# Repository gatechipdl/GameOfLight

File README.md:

# GameOfLight
Game of Light Installation

## Requirements
- 36 stations
- each station 1m in lenght covered in leds
- 5 sections of lamp to create a 'species'
- automatic identification of each lamp 'species'

## Location
- Hyatt Regency Denver at Co Convention Center
    - [Floorplans](https://denver.regency.hyatt.com/hyatt/images/hotels/dencc/floorplan.pdf)

## Main Power Supply
- 12,24V power supply recommended with a buck converter (for leds and mcu) or linear regulator (if for just mcu) at each location
- typical computer psu will have several 12V rails. A [modular](https://www.amazon.com/EVGA-Supernova-120-G1-1000-VR-Modular-Supply/dp/B00CGYCNG2) psu would be best for ensuring enough 12V rails without extra wiring.
- if there is 5m of leds with 30 leds/meter wrapped around a tube, then that is 150 leds. 150 leds at 60mA is 9A running at around 3V. This is around 27-30W assuming an efficient local conversion of power, which is likely embedded within the addressable chip.
- 36 stations of 30W is a total max draw of 1080W. So a 800W-1000W-1200W power supply should be fine.

## Local Power Regulation
- Switch mode power supply for high current, such as this [300W Step Down Regulator](https://www.aliexpress.com/item/DC-CC-12A-300W-Step-Down-Buck-Converter-7-32V-To-0-8-28V-Power-module/32247251105.html)
- Linear regulator for low current needs (eg. if using 12V main power supply and 12V leds)

## Power Distribution Connectors
- ribbon cable (40 pin), using most pins for power and ground
- RJ45 can only handle up to 1A
- RJ11 can only handle up to 1A
- 5557 molex need to crimp; not designed to be removed often;
- DC Barrel Jack 5.5mm, most connectors designed for 3A, but can get special ones for laptaps that can handle 8A
- [6 pin Pluggable Screw Terminal](https://www.aliexpress.com/item/Free-shipping-5-sets-ht5-08-6pin-Terminal-plug-type-300V-10A-5-08mm-pitch-connector/32667091061.html)
    - 12V - GND - DataMinus - DataPlus - GND - 12V
- [7 pin Pluggable Screw Terminal](https://www.aliexpress.com/item/Free-shipping-5-sets-ht5-08-7pin-Terminal-plug-type-300V-10A-5-08mm-pitch-connector/32665369867.html)
    - 12V - GND - DataMinus - GND - DataPlus - GND - 12V
    - extra ground in middle is for connecting ground to the main controller in the case that the main controller is not using the same ground as the stations' ground from the main power supply. For example if the main controller is run by or powered by a laptop.

## Power Distribution Wiring
- [$27 100 ft. 14/2 White Solid SIMpull NM-B Wire](http://www.homedepot.com/p/Romex-100-ft-14-2-White-Solid-SIMpull-NM-B-Wire-28827428/202316379)
- [$38 100 ft. 14-2 Black Stranded Landscape Lighting Cable](http://www.homedepot.com/p/Southwire-100-ft-14-2-Black-Stranded-Landscape-Lighting-Cable-55213243/202316247)
- [$16 100' Feet 14 Gauge Red Black Stranded 2 Conductor Speaker Wire Car Home Audio Ga](https://www.amazon.com/Gauge-Black-Stranded-Conductor-Speaker/dp/B00J36SUWC)
- [$26 eXtreme Products 2 Conductor 14 Gauge Stranded Copper Core Speaker Wire (No Aluminum Core) for Home Theater Speakers Radio Speakers Car Audio or Any Audio Interface - 100 Foot Clear Coat](https://www.amazon.com/eXtreme-Conductor-Speaker-Wire-Interface/dp/B01HBWJ1HM)

## Signal Distribution Wiring
- for RS485 we need overall impedance of 120 ohms. For our distances, lighter gauges are fine, but [this](http://www.chipkin.com/rs485-cables-why-you-need-3-wires-for-2-two-wire-rs485/) recommends 24AWG or heavier. [Here are more recommendations](http://www.bb-elec.com/Learning-Center/All-White-Papers/Serial/Cable-Selection-for-RS422-and-RS485-Systems/Cable-Selection-for-RS-422-and-RS-485-Systems.PDF).
- Two wire or Three wire. May need three wire to include an additional ground in the case that the main controller is not using the same ground as the stations' power ground from the main power supply. This could be the case with a laptop for example.
- [$13 Ethernet Cable (100 Feet)](https://www.amazon.com/Mediabridge-Ethernet-Cable-100-Feet/dp/B003RCEAB8), cut and pull out twisted pair wires
- [$23 100-Feet 24-Gauge 4 Pair Cat 5e](https://www.amazon.com/Southwire-56917643-100-Feet-Outdoor-CMR-75-Degree/dp/B005V0BJ1S)

## LEDs
- addressable color leds
- could use 1 2m strip folded over
- could use 1 5m strip wrapped around a pole (this will provide more light)
- WS2811 with 3 color leds on each section, each led is rgb, but in clusters of 3. This is fine for our applications. Also these are 12V, which is better for current draw. [$8-10 per 5m strip](https://www.aliexpress.com/item/best-price-5m-DC12V-ws2811ic-5050-RGB-SMD-individually-addressable-ws2811-led-pixels-strip/32385533484.html)

## Control
- recommended individual controller for each station; otherwise refresh rate is likely to be very slow
- attiny85 possible? may not have enough pins; but might
- atmega328p?
- arduino pro mini clone ($1-2)
- 1 master device with 36 other devices. The master controls the CA simulation and dictates the animation colors and patterns to each of the 36 stations.
    - however, it is possible to have the 36 devices run the simulation themselves, with each device getting data about it's neighbors, and computing the next step and selecting it's own animation. This would also require that they all synchronize, to some degree on an update algorithm. This could be done. Would be really nice to have. This is something we could first develop in the master/slave configuration, and then later spend time developing the slave-only method if there is time. The slave-only would really connect conceptually rather than having any kind of single master.

## Recognition
- manual input (what a drag)
- infrared linear quadrature encoder or similar to recognize the lamp 'species' as a barcode when the lamp shade is slide over the rod
    - this would argue for a separate controller on each station
- IR Distance Sensor
    - [XK-GK-5010A](https://www.aliexpress.com/item/Hot-Sale-Short-Distance-Sensor-Induction-Switch-Dual-Functions-Ir-Sensor-Switch-Active-Performance-Modules-Board/32769983297.html)
    - [TCRT5000 Sensor](https://www.aliexpress.com/item/20-pcs-TCRT5000L-TCRT5000-Reflective-Optical-Sensor-Infrared-IR-Photoelectric-Switch/1909098476.html)
    - [TCRT5000 Module with Pot](https://www.aliexpress.com/item/Free-shipping-Line-Track-Sensor-TCRT5000-Infrared-Reflective-IR-Photoelectric-Switch-Barrier/32517344067.html) [3D model](http://www.stlfinder.com/model/line-finder-tcrt5000/4505787) 32mmx14mm
    - [TCRT5000 Module Digital Only](https://www.aliexpress.com/item/New-TCRT5000-Line-Track-Sensor-Module-Reflection-Infrared-Sensor-Switch-Module-For-Arduino-5pcs-lot-Free/32359412782.html)
    - [TCRT5000 Module Analog Only](https://www.aliexpress.com/item/10PCS-IR-Infrared-Line-Track-Follower-Sensor-TCRT5000-Obstacle-Avoidanc-For-Arduino/32672744833.html)
    - [4 Channel Line Follower](https://www.aliexpress.com/item/Free-shipping-4-way-infrared-tracing-line-follow-tracking-obatacle-avoidance-Sensor-Module-for-Aduino-Robot/32645816426.html)
    - [8 Channel Line Follower](https://www.aliexpress.com/item/8-Channel-High-Precision-Infrared-Detection-Tracking-Sensor-Moudle-For-Arduino-Raspberry-Pi-Car-Robot-TCRT5000/32714804808.html)

## Communication
- if using multiple controllers, one on each station, using a [multidrop bus](https://en.wikipedia.org/wiki/Multidrop_bus) rather than a shift/ring topology
- I2C can go about [20ft](http://forum.arduino.cc/index.php?topic=57604.0) without additional driver or buffers
- RS-232 can go about [50ft](https://www.lammertbies.nl/comm/info/RS-232_specs.html)
- RS-422 can go about 5000ft, but is single driver/master, and up to 10 receivers. It is differential, so it's more noise immune than rs232, but the primary downside is it is one directional communcation
- RS-485 can go about [4000ft](http://www.bb-elec.com/Learning-Center/All-White-Papers/Serial/Basics-of-the-RS-485-Standard.aspx)
    - RS-485 to ttl converter using the MAX485CSA
    - $0.38 [Module](https://www.aliexpress.com/item/MAX485-Module-RS-485-TTL-to-RS485-MAX485CSA-Converter-Module-For-Arduino-Integrated-Circuits-Products/32667981058.html)
    - needs twisted pair wire (same as RS422); actually can go without twisted pair if run is shorter, so this isn't completely necessary
    - downside is that RS485 supports up to 32 devices. But I don't think that is built into the protocol. We should be able to go over that. As each device will have it's own way of identifying itself. I think 32 devices is more of a guideline.
    - RS-485 might need a 3.3V version like the [SP3485 Module](https://www.aliexpress.com/item/3-3V-UART-serial-to-RS485-SP3485-Transceiver-Converter-Communication-Module/32224154908.html). This board is lower cost than if we were to purchase just the chip and integrate it into our own design.

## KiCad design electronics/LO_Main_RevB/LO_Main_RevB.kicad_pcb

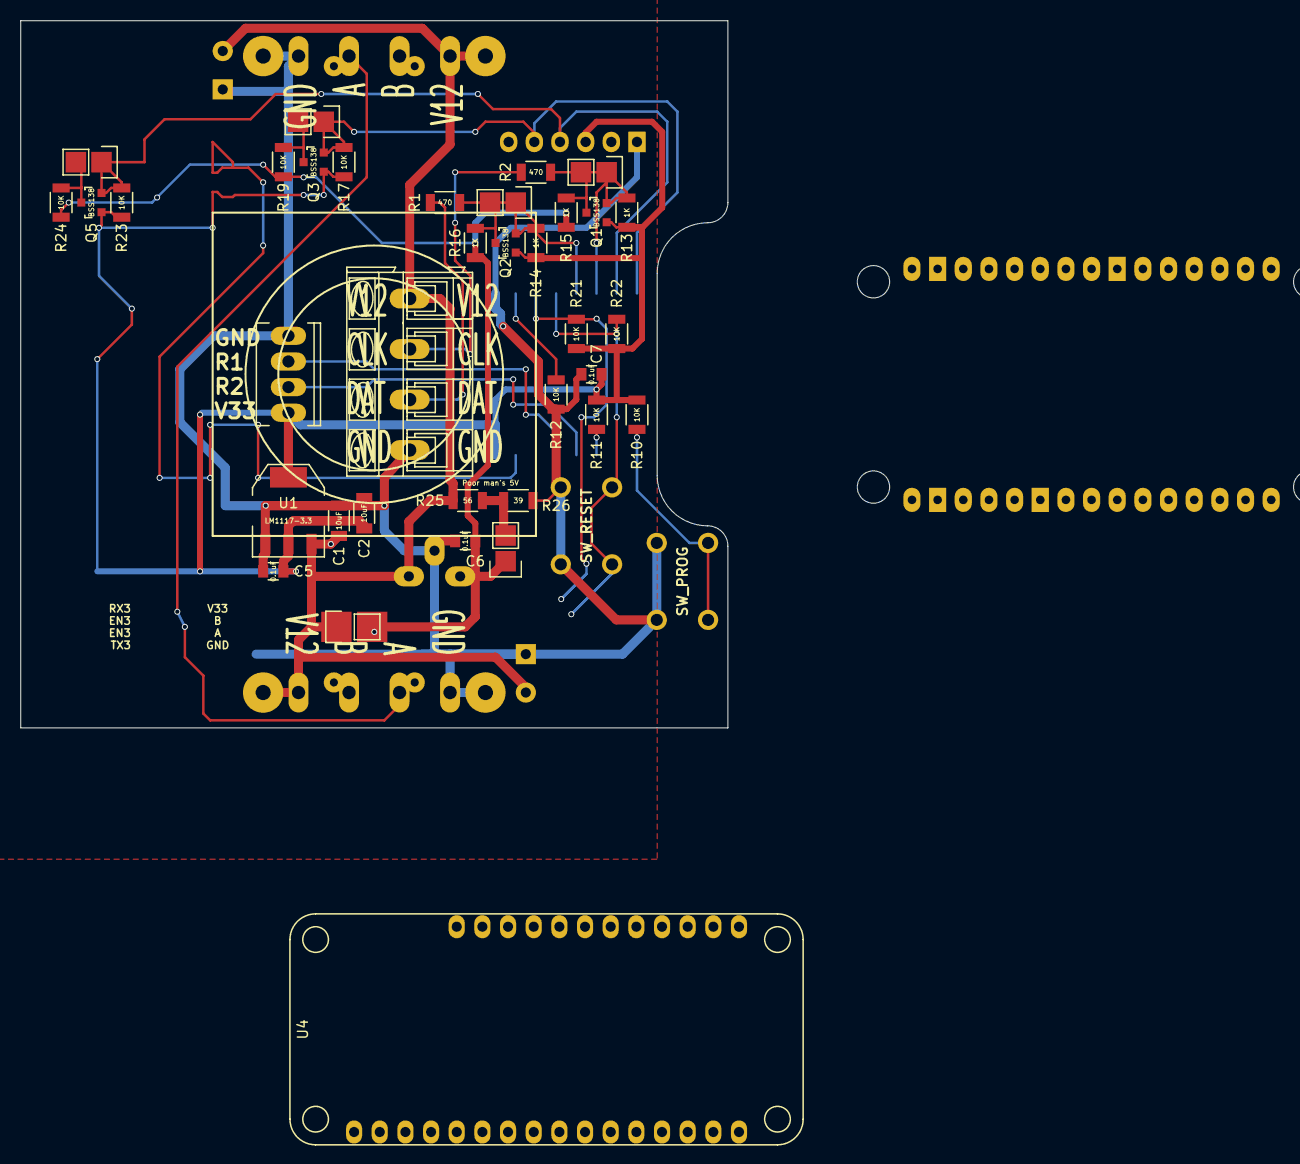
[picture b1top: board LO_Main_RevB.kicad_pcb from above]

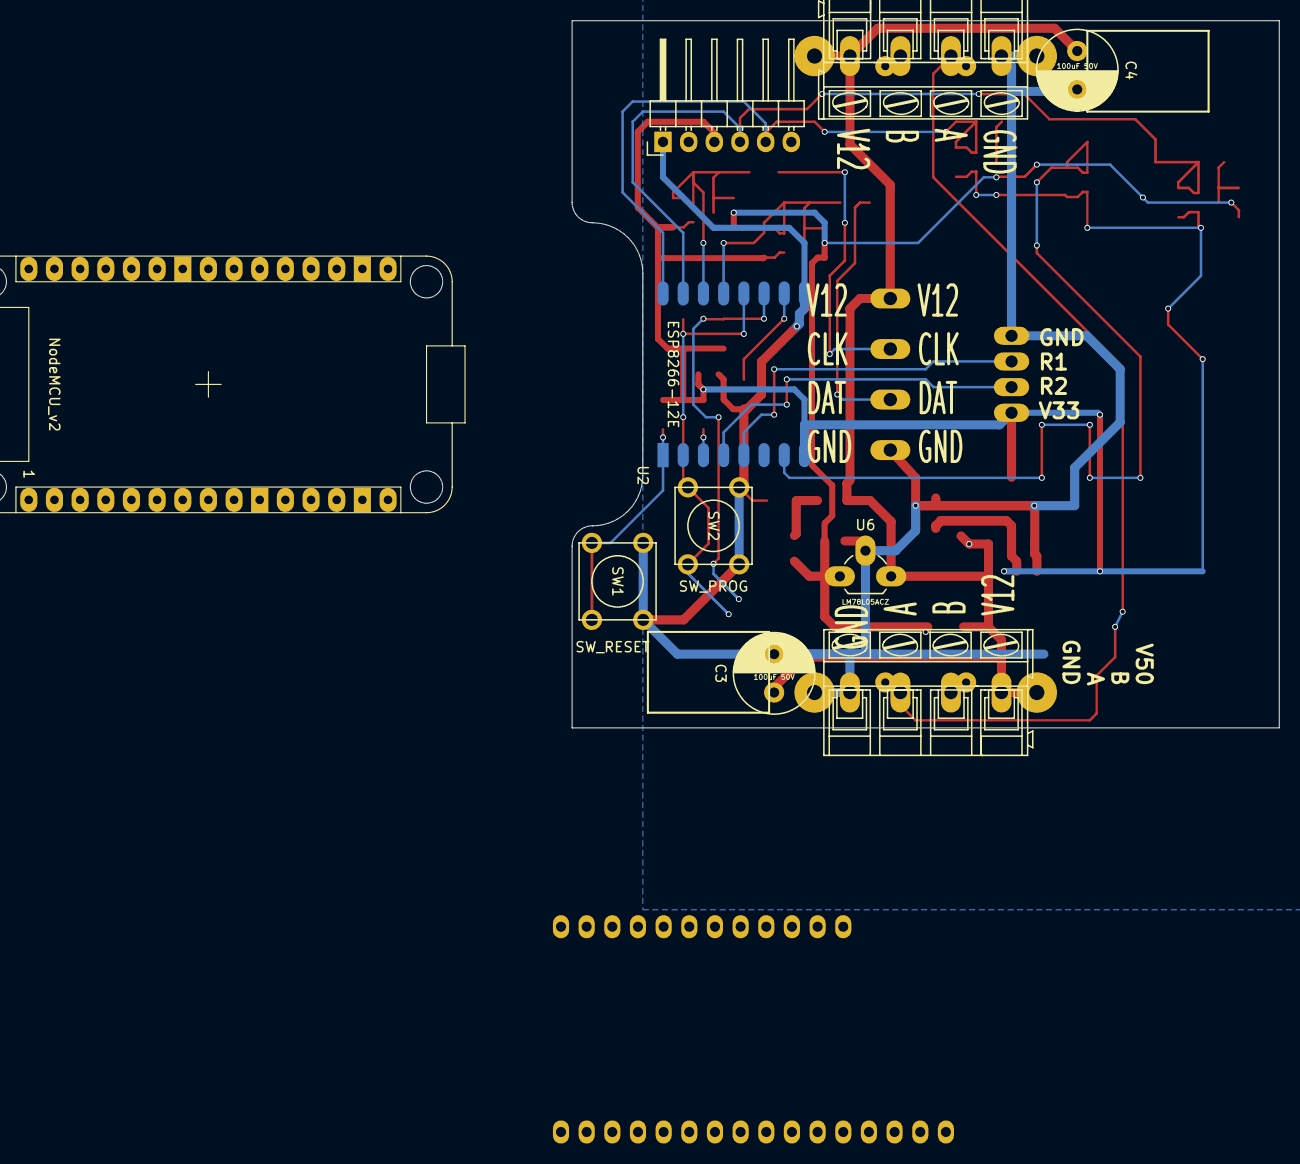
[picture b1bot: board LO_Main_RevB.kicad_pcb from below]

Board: 2 copper layers, 70.0 x 70.0 mm, 54 parts (10 on the bottom side), 20 nets.

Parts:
C1, C2: 10uF; C_1206
C3, C4: 100uF 50V; C_Radial_D8_L13_P3.8
C5, C6, C7: 0.1uF; C_0805
P3: CONN_READERS; Socket_MOLEX-KK-RM2-54mm_Lock_4pin_straight
P5: CONN_MAIN1; AK300-4
P6: CONN_MAIN2; AK300-4
P12: CONN_LED; AK300-4
P13: FTDI; Pin_Header_Angled_1x06
P14: CONN_V50SEL; Pin_Header_Straight_1x02
P16: CONN_V12V50; Pin_Header_Straight_1x02
P17: CONN_LEDCLK; Pin_Header_Straight_1x02
P18: CONN_LEDDATA; Pin_Header_Straight_1x02
P19: CONN_TX3350; Pin_Header_Straight_1x02
P21: CONN_RX3350; Pin_Header_Straight_1x02
P22, P26: CONN_GND; SolderWirePad_single_1-5mmDrill
P23, P27: CONN_A; SolderWirePad_single_0-8mmDrill
P24, P28: CONN_B; SolderWirePad_single_0-8mmDrill
P25, P29: CONN_V12; SolderWirePad_single_1-5mmDrill
Q1, Q2, Q3, Q5: BSS138; SOT-23
R1, R2: 470; R_1206
R10, R11, R12, R17, R19, R21, R22, R23, R24: 10K; R_1206
R13, R14, R15, R16: 1K; R_1206
R25: 56; R_1206
R26: 39; R_1206
SW1: SW_RESET; SW_PUSH_SMALL
SW2: SW_PROG; SW_PUSH_SMALL
U1: LM1117-3.3; SOT-223
U2: ESP8266-12E; ESP-12E
U3: NodeMCU_v2
U4: HUZZAH_Feather
U6: LM78L05ACZ; TO-92_Rugged

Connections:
GND: C1.2, C2.2, C3.2, C4.2, C5.2, C6.2, C7.2, P3.1, P5.1, P6.1, P12.1, P13.1, P22.1, P26.1, R12.1, R26.1, SW1.2, SW2.2, U1.1, U2.15, U6.2
GPIO0: R22.1, SW2.1, U2.18
GPIO2: R21.1, U2.17
GPIO15: R12.2, U2.16
LED_CLOCK: P17.1, P17.2, Q1.2, Q1.3, R2.1, R13.1, R15.1, U2.20
LED_DATA: P18.1, P18.2, Q2.2, Q2.3, R1.1, R14.1, R16.1, U2.19
unnamed: P12.2, R1.2
unnamed: P12.3, R2.2
unnamed: R11.1, U2.3
READER1: P3.2, U2.5
READER2: P3.3, U2.4
RESET: R10.1, SW1.1, U2.1
RX33: P13.4, P21.1, Q5.2, R23.1, U2.21
RX50: P21.2, Q5.3, R24.1
TX33: P13.5, P19.1, Q3.2, R17.1, U2.22
TX50: P19.2, Q3.3, R19.1
V12: C1.1, C3.1, C4.1, P5.4, P6.4, P12.4, P16.1, P25.1, P29.1, R25.2, U1.3, U6.3
V33: C2.1, C5.1, C7.1, P3.4, P13.3, Q1.1, Q2.1, Q3.1, Q5.1, R10.2, R11.2, R13.2, R14.2, R17.2, R21.2, R22.2, R23.2, U1.2, U1.4, U2.8
V50: C6.1, P14.1, P16.2, R15.2, R16.2, R19.2, R24.2, U6.1
V50D: P14.2, R25.1, R26.2

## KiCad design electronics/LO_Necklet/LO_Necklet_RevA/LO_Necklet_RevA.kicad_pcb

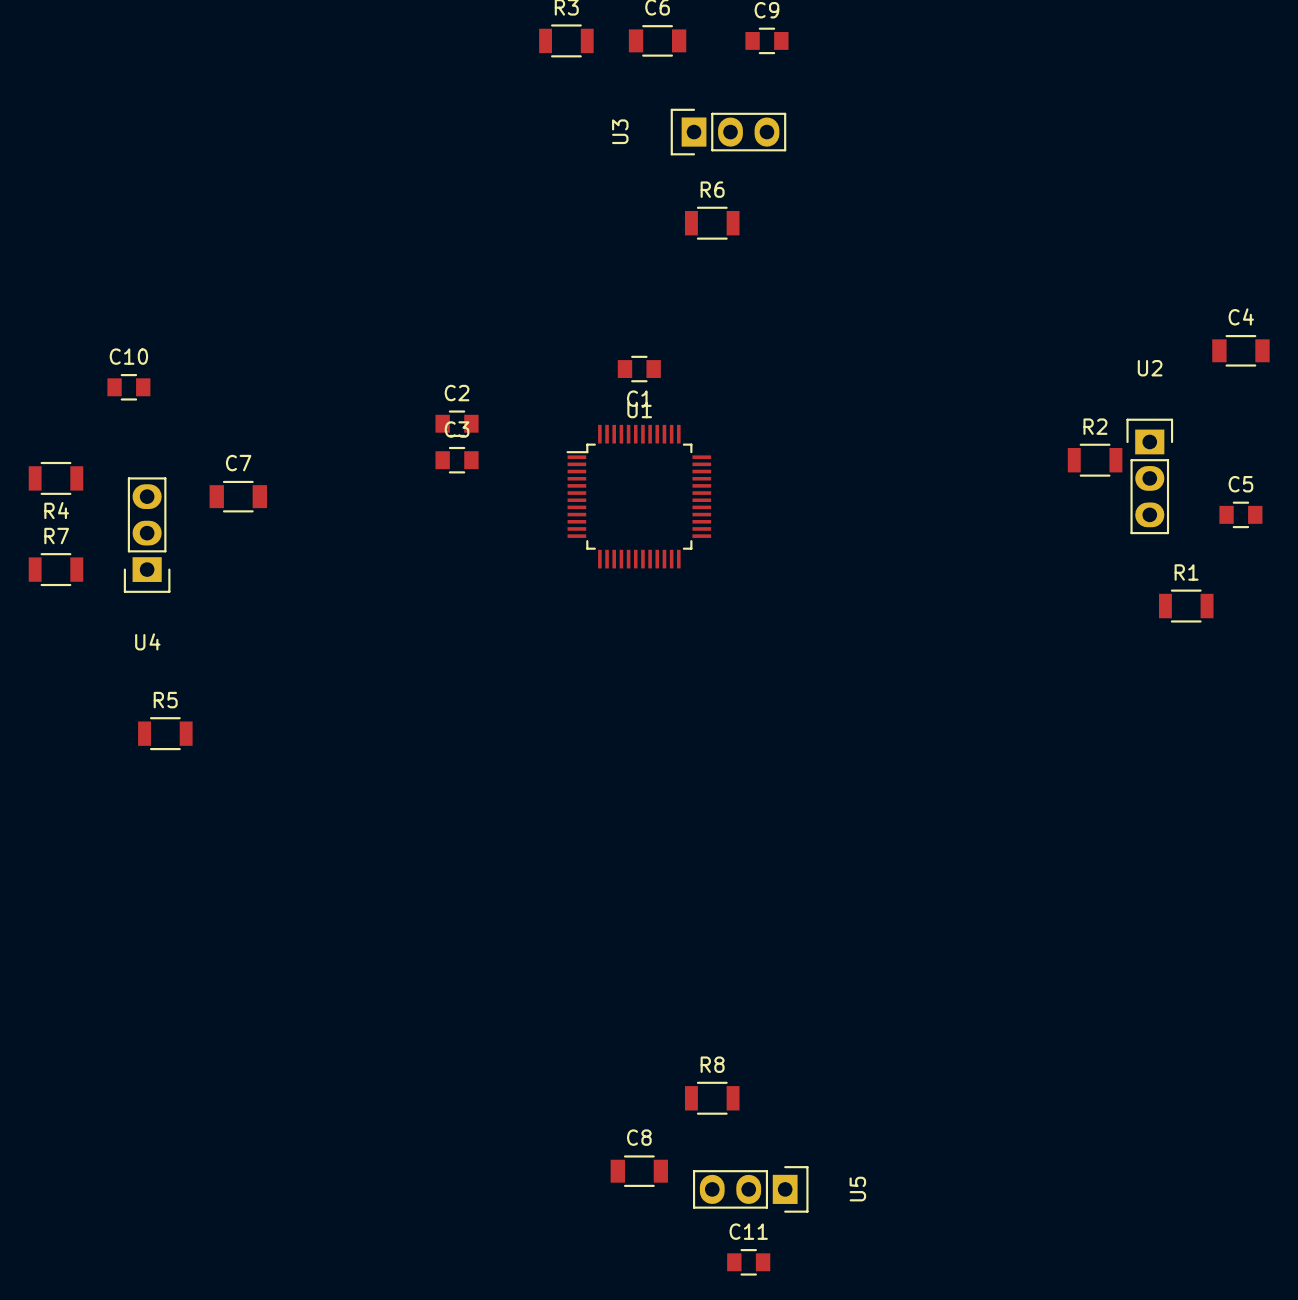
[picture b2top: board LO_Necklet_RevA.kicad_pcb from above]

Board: 2 copper layers, 24 parts (0 on the bottom side), 13 nets, no tracks yet.

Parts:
C1: 1uF; C_0805
C2, C3: 22pF; C_0805
C4, C6, C7, C8: 100uF; C_1206
C5, C9, C10, C11: 0.1uF; C_0805
R1, R3, R4, R5: 100; R_1206
R2, R6, R7, R8: 10K; R_1206
U1: SAMD20G18A-A; TQFP-48_7x7mm_Pitch0.5mm
U2, U3, U4, U5: VS18388; Pin_Header_Straight_1x03

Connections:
GND: C1.1, C2.1, C3.1, C4.2, C5.2, C6.2, C7.2, C8.2, C9.2, C10.2, C11.2, U1.5, U1.18, U1.35, U1.42, U2.2, U3.2, U4.2, U5.2
IRIN1: R2.2, U2.1
IRIN2: R6.2, U3.1
IRIN3: R7.2, U4.1
IRIN4: R8.2, U5.1
unnamed: C1.2, U1.43
unnamed: C2.2, U1.1
unnamed: C3.2, U1.2
unnamed: C4.1, C5.1, R1.2, R2.1, U2.3
unnamed: C6.1, C9.1, R3.2, R6.1, U3.3
unnamed: C7.1, C10.1, R4.2, R7.1, U4.3
unnamed: C8.1, C11.1, R5.2, R8.1, U5.3
V33: R1.1, R3.1, R4.1, R5.1, U1.6, U1.17, U1.36, U1.44

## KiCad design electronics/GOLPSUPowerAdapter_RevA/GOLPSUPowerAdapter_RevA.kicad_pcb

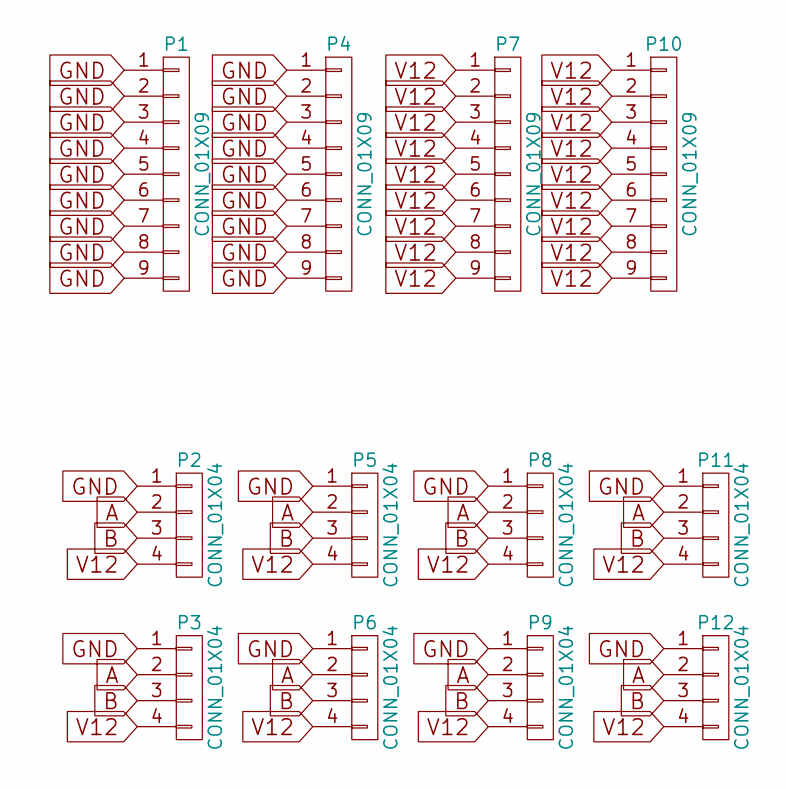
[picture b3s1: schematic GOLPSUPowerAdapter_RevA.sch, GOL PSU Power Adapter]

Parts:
P1, P4, P7, P10: CONN_01X09; TerminalBlock_Pheonix_PT-3.5mm_9pol
P2, P3, P5, P6, P8, P9, P11, P12: CONN_01X04; AK300-4

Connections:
A: P2.2, P3.2, P5.2, P6.2, P8.2, P9.2, P11.2, P12.2
B: P2.3, P3.3, P5.3, P6.3, P8.3, P9.3, P11.3, P12.3
GND: P1.1, P1.2, P1.3, P1.4, P1.5, P1.6, P1.7, P1.8, P1.9, P2.1, P3.1, P4.1, P4.2, P4.3, P4.4, P4.5, P4.6, P4.7, P4.8, P4.9, P5.1, P6.1, P8.1, P9.1, P11.1, P12.1
V12: P2.4, P3.4, P5.4, P6.4, P7.1, P7.2, P7.3, P7.4, P7.5, P7.6, P7.7, P7.8, P7.9, P8.4, P9.4, P10.1, P10.2, P10.3, P10.4, P10.5, P10.6, P10.7, P10.8, P10.9, P11.4, P12.4

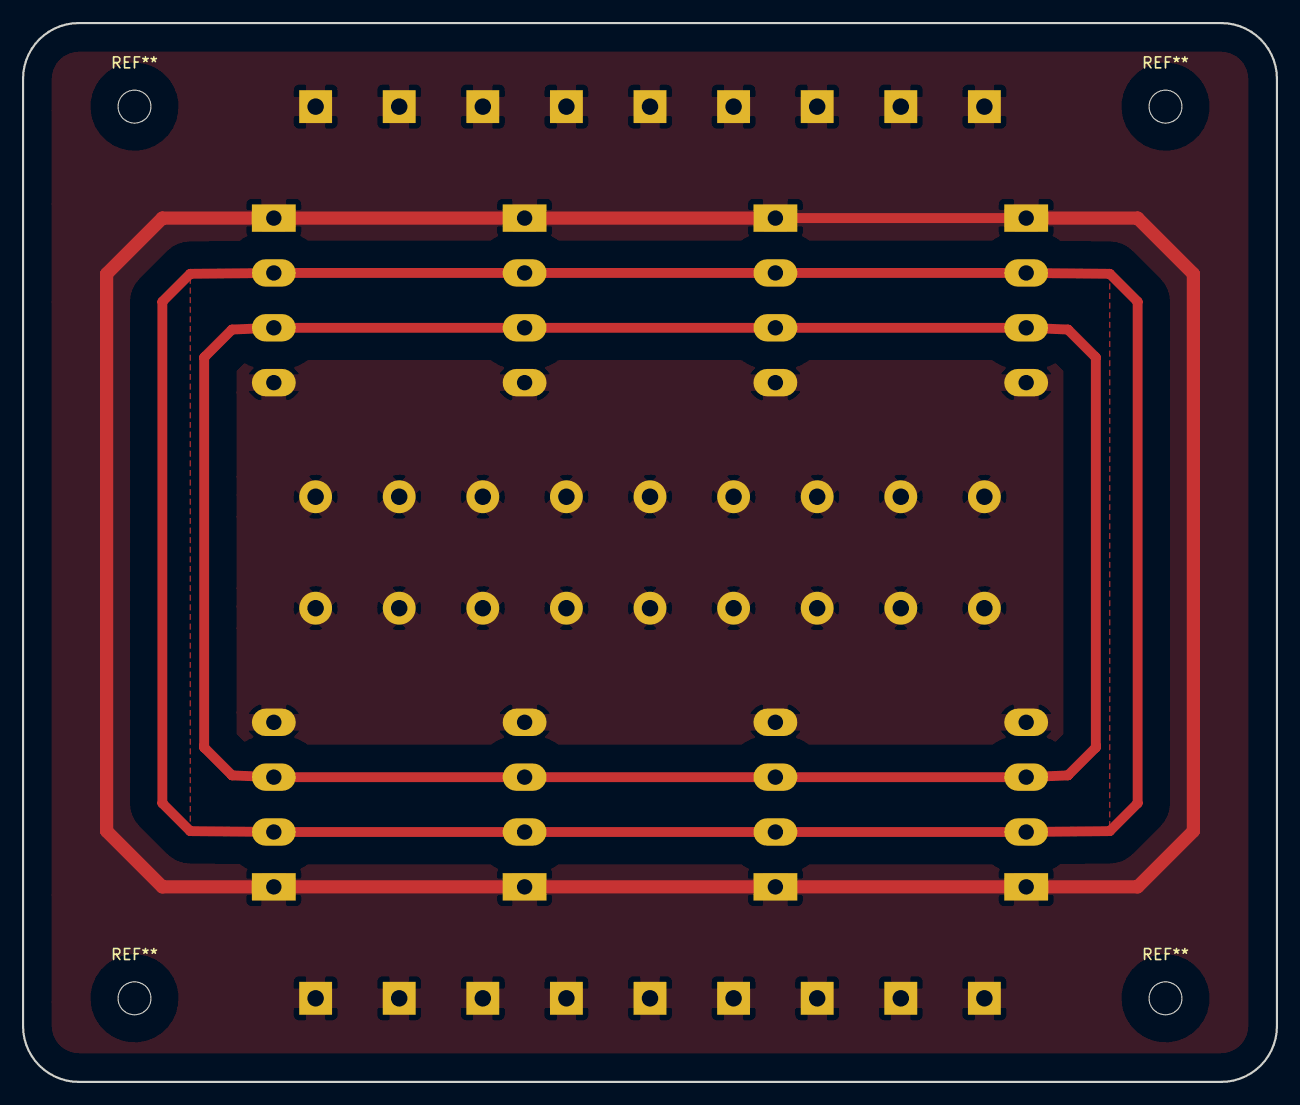
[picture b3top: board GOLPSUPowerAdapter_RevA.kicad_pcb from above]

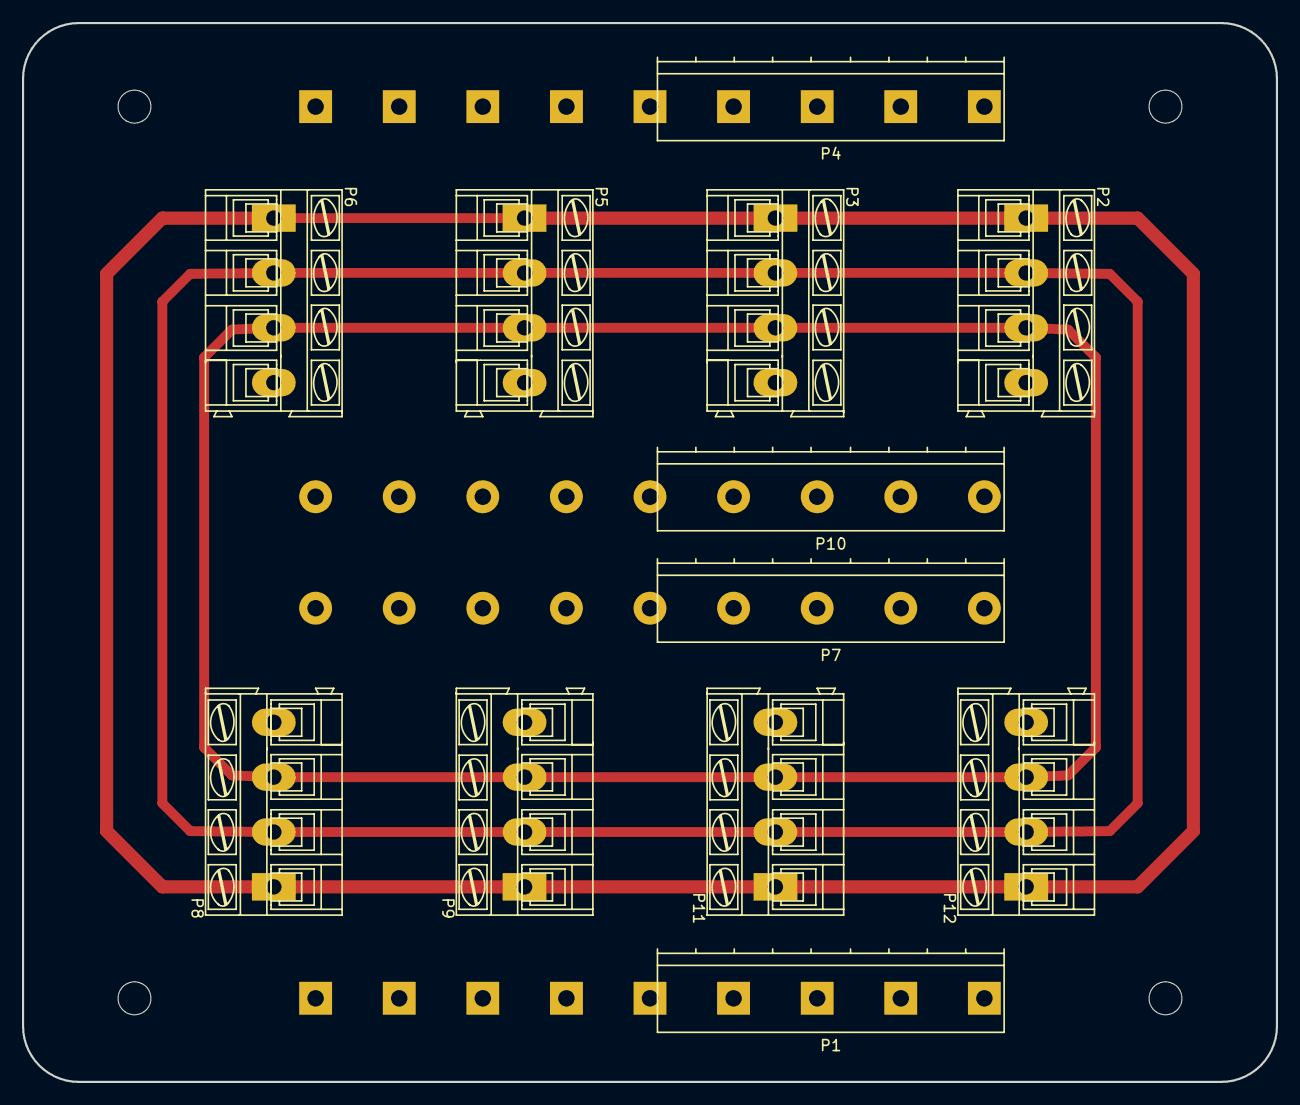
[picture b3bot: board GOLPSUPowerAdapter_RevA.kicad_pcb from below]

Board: 2 copper layers, 114.3 x 96.5 mm, 12 parts (12 on the bottom side), 4 nets.

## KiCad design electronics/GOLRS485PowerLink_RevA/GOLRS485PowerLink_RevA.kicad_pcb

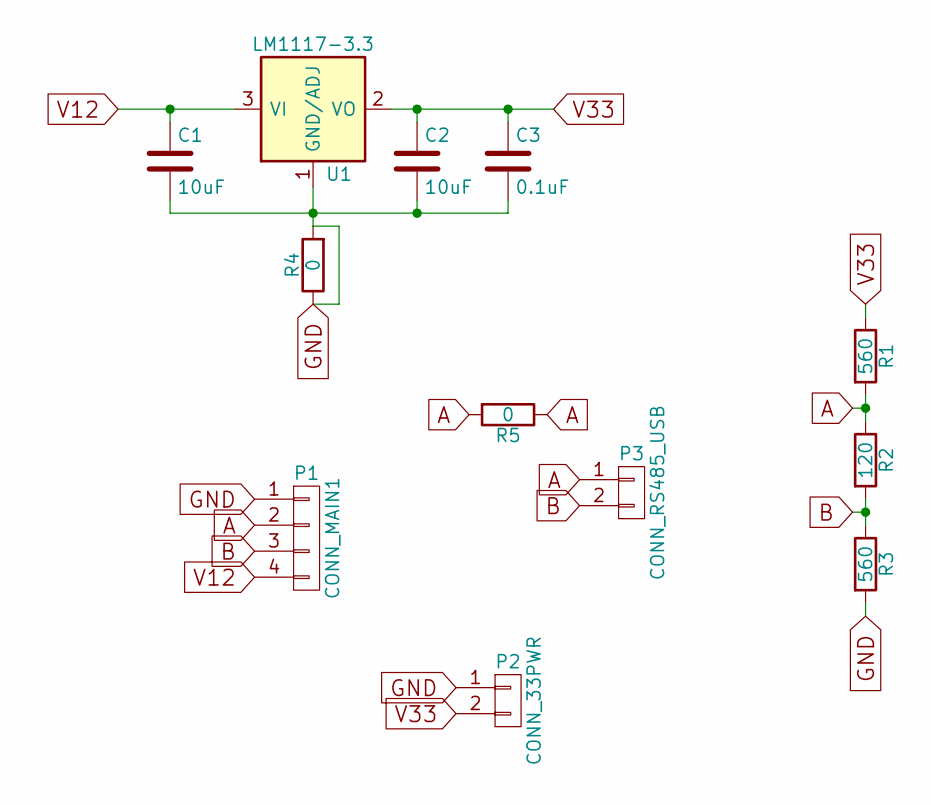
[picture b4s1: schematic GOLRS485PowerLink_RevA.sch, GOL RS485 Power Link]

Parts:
C1, C2: 10uF; C_1206
C3: 0.1uF; C_0805
P1: CONN_MAIN1; AK300-4
P2: CONN_33PWR; Pin_Header_Straight_1x02
P3: CONN_RS485_USB; AK300-2
R1, R3: 560; Resistor_SMD+THTuniversal_1206_RM10_HandSoldering
R2: 120; Resistor_SMD+THTuniversal_1206_RM10_HandSoldering
R4: 0; Resistor_SMD+THTuniversal_2512_RM10_HandSoldering
R5: 0; Resistor_SMD+THTuniversal_1206_RM10_HandSoldering
U1: LM1117-3.3; SOT-223

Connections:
A: P1.2, P3.1, R1.2, R2.1, R5.1, R5.2
B: P1.3, P3.2, R2.2, R3.1
GND: C1.2, C2.2, C3.2, P1.1, P2.1, R3.2, R4.1, R4.2, U1.1 (GND/ADJ)
V12: C1.1, P1.4, U1.3 (VI)
V33: C2.1, C3.1, P2.2, R1.1, U1.2 (VO), U1.4 (VO)

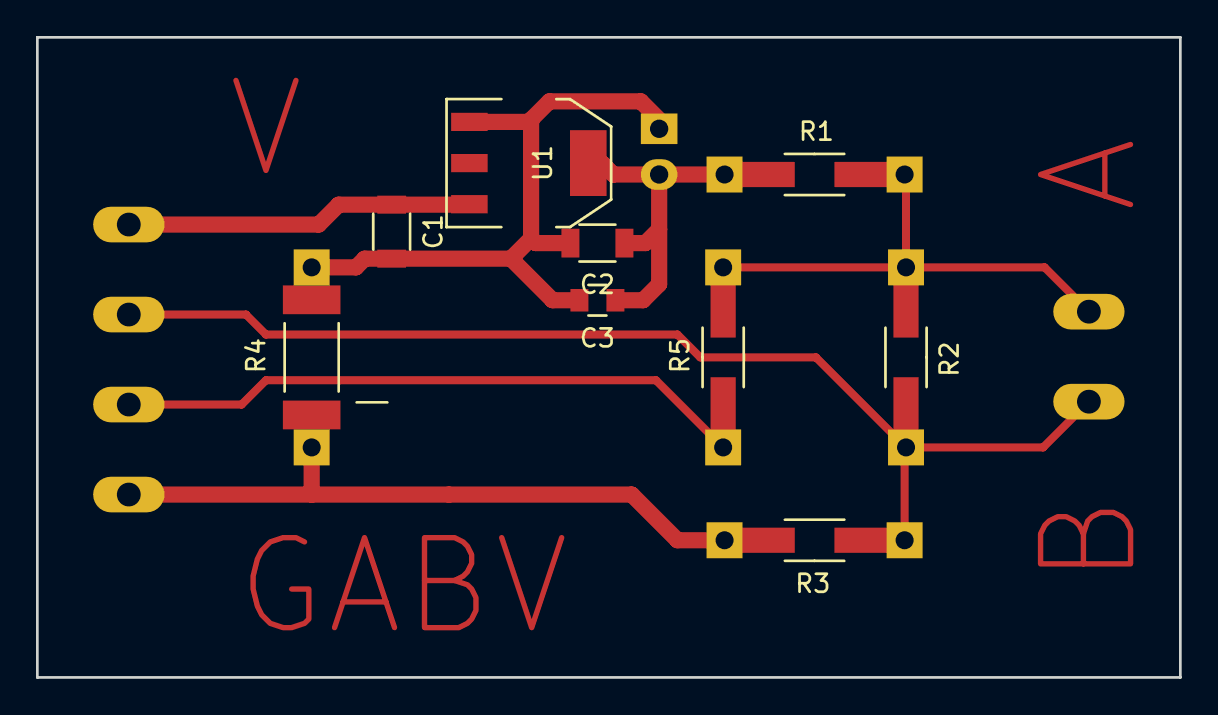
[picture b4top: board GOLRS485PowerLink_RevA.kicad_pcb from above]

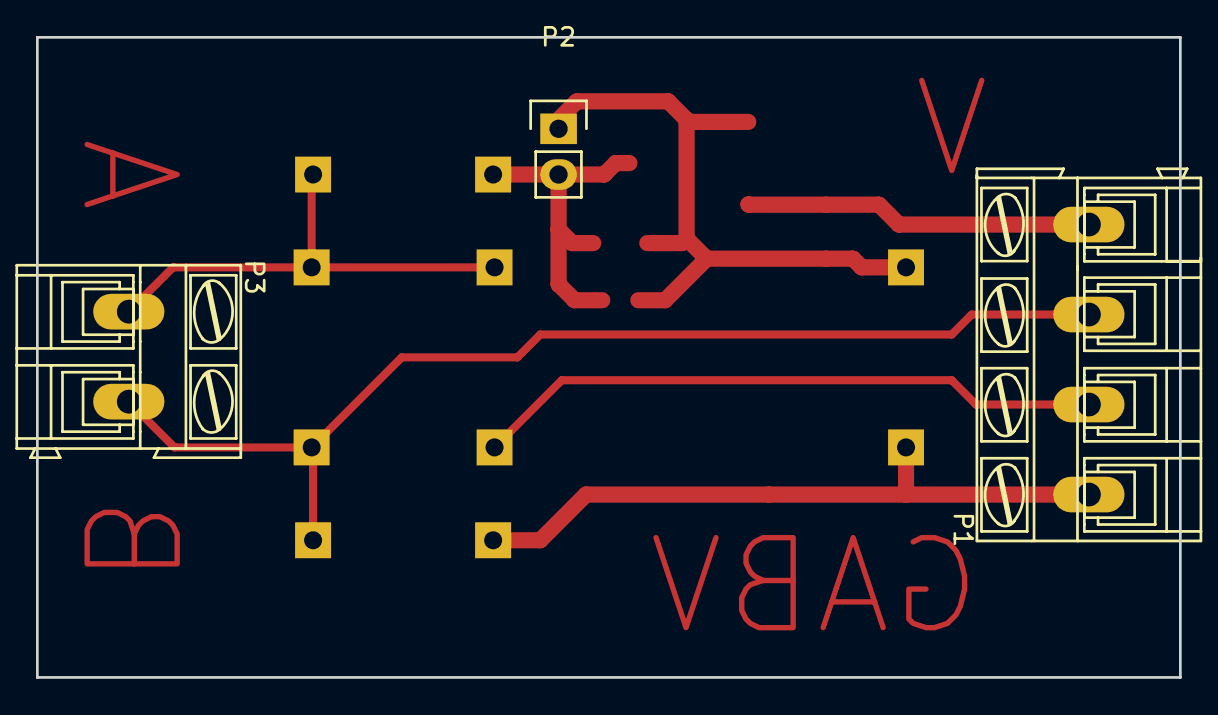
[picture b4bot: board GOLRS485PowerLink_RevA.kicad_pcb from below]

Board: 2 copper layers, 63.5 x 35.6 mm, 12 parts (3 on the bottom side), 5 nets.

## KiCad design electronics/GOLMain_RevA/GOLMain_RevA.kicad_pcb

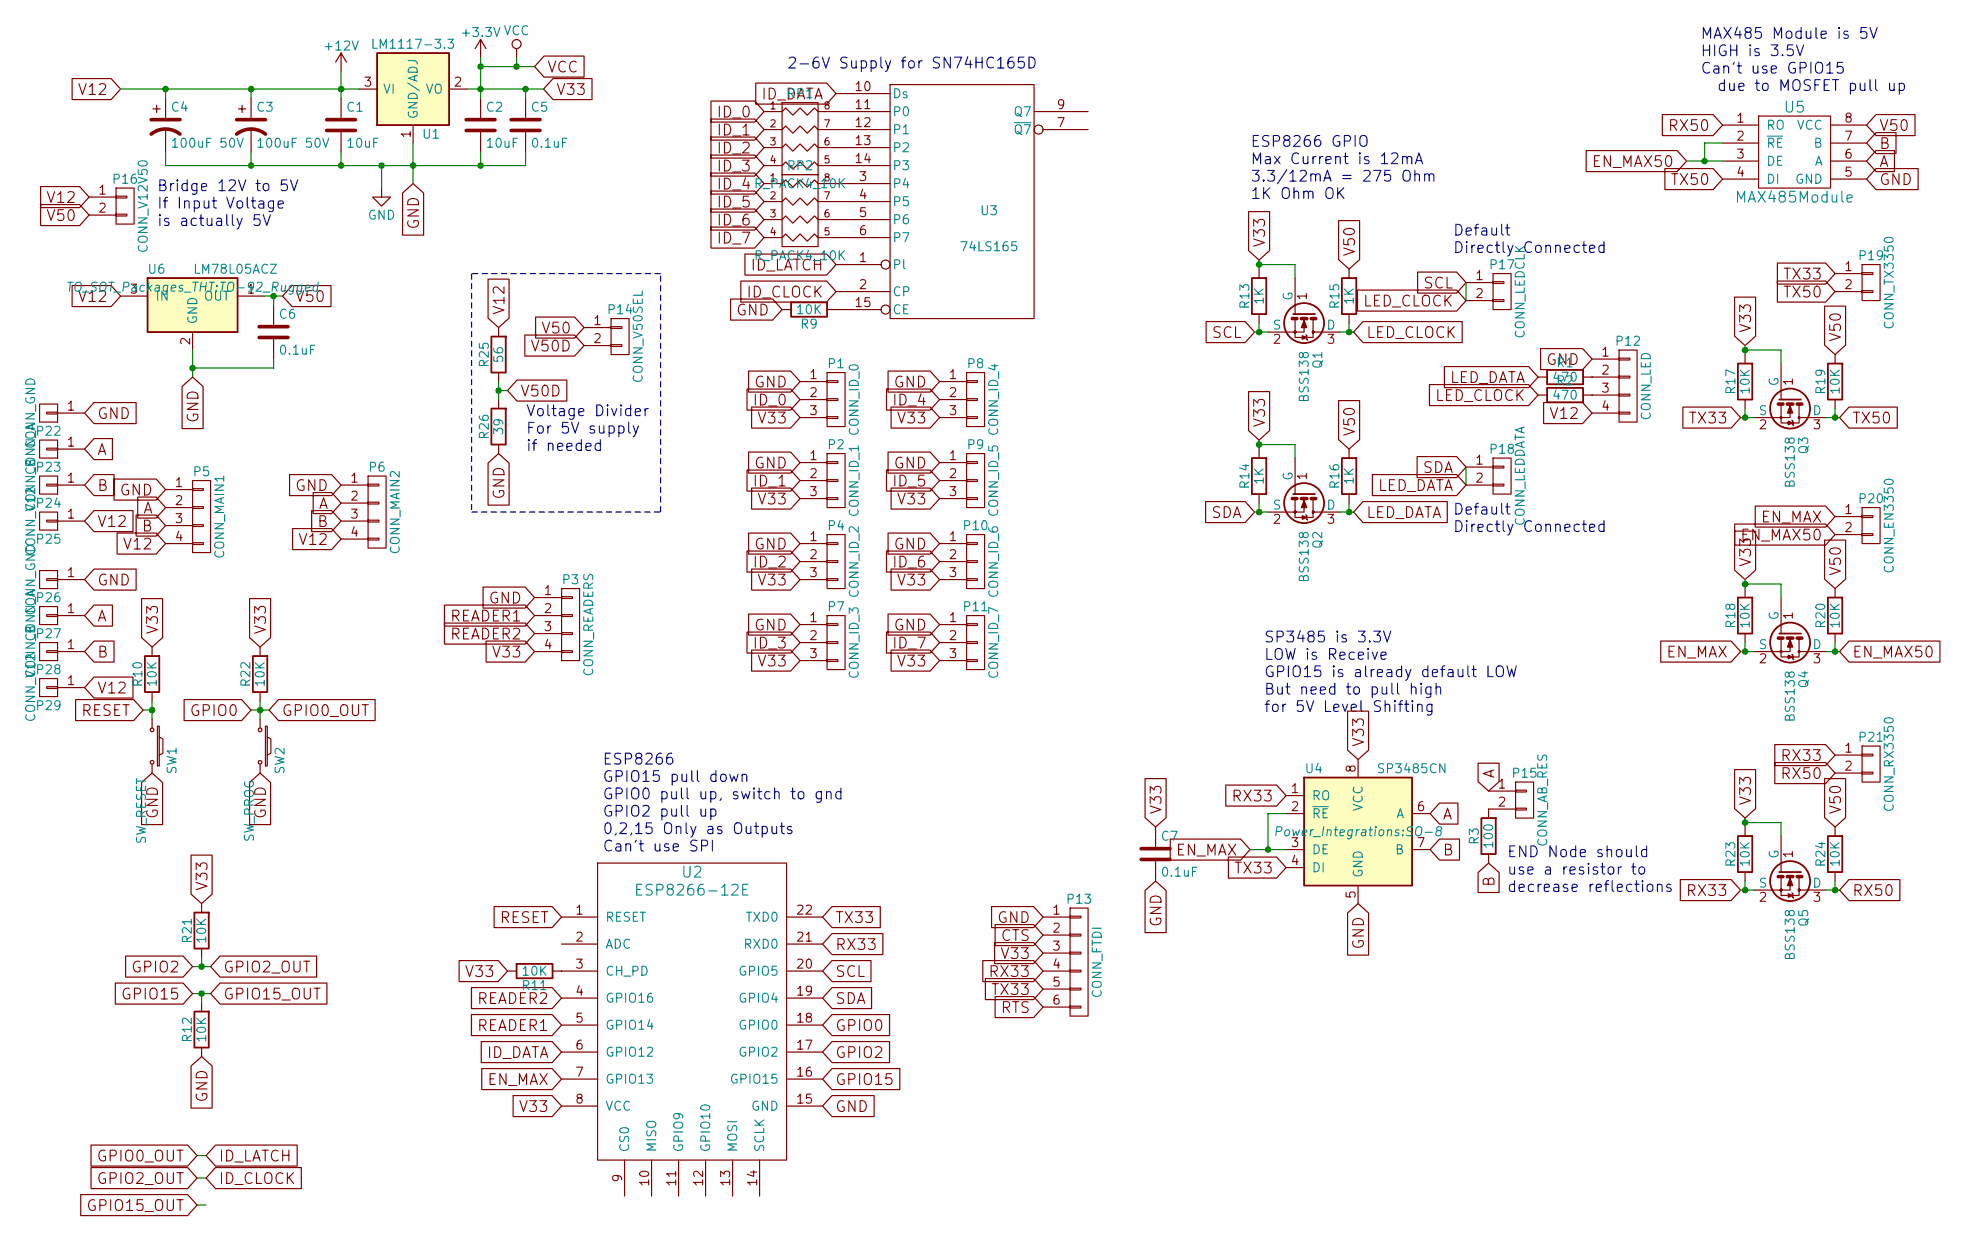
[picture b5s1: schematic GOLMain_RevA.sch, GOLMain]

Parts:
C1, C2: 10uF; C_1206
C3, C4: 100uF 50V; C_Radial_D8_L13_P3.8
C5, C6, C7: 0.1uF; C_0805
P1: CONN_ID_0; Pin_Header_Straight_1x03
P2: CONN_ID_1; Pin_Header_Straight_1x03
P3: CONN_READERS; Socket_MOLEX-KK-RM2-54mm_Lock_4pin_straight
P4: CONN_ID_2; Pin_Header_Straight_1x03
P5: CONN_MAIN1; AK300-4
P6: CONN_MAIN2; AK300-4
P7: CONN_ID_3; Pin_Header_Straight_1x03
P8: CONN_ID_4; Pin_Header_Straight_1x03
P9: CONN_ID_5; Pin_Header_Straight_1x03
P10: CONN_ID_6; Pin_Header_Straight_1x03
P11: CONN_ID_7; Pin_Header_Straight_1x03
P12: CONN_LED; AK300-4
P13: CONN_FTDI; Pin_Header_Angled_1x06
P14: CONN_V50SEL; Pin_Header_Straight_1x02
P15: CONN_AB_RES; Pin_Header_Straight_1x02
P16: CONN_V12V50; Pin_Header_Straight_1x02
P17: CONN_LEDCLK; Pin_Header_Straight_1x02
P18: CONN_LEDDATA; Pin_Header_Straight_1x02
P19: CONN_TX3350; Pin_Header_Straight_1x02
P20: CONN_EN3350; Pin_Header_Straight_1x02
P21: CONN_RX3350; Pin_Header_Straight_1x02
P22, P26: CONN_GND; SolderWirePad_single_1-5mmDrill
P23, P27: CONN_A; SolderWirePad_single_0-8mmDrill
P24, P28: CONN_B; SolderWirePad_single_0-8mmDrill
P25, P29: CONN_V12; SolderWirePad_single_1-5mmDrill
Q1, Q2, Q3, Q4, Q5: BSS138; SOT-23
R1, R2: 470; R_1206
R3: 100; R_1206
R9, R10, R11, R12, R17, R18, R19, R20, R21, R22, R23, R24: 10K; R_1206
R13, R14, R15, R16: 1K; R_1206
R25: 56; R_1206
R26: 39; R_1206
RP1, RP2: R_PACK4_10K; R_Array_Convex_4x1206
SW1: SW_RESET; SW_PUSH_SMALL
SW2: SW_PROG; SW_PUSH_SMALL
U1: LM1117-3.3; SOT-223
U2: ESP8266-12E; ESP-12E
U3: 74LS165; SOIC-16_3.9x9.9mm_Pitch1.27mm
U4: SP3485CN; SO-8
U5: MAX485Module; DIP-8_W7.62mm_LongPads
U6: LM78L05ACZ; TO-92_Rugged

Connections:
A: P5.2, P6.2, P15.1, P23.1, P27.1, U4.6 (A), U5.6 (A)
B: P5.3, P6.3, P24.1, P28.1, R3.1, U4.7 (B), U5.7 (B)
EN_MAX: P20.1, Q4.2 (S), R18.1, U2.7 (GPIO13), U4.2 (~RE~), U4.3 (DE)
EN_MAX50: P20.2, Q4.3 (D), R20.1, U5.2 (~RE), U5.3 (DE)
GND: C1.2, C2.2, C3.2, C4.2, C5.2, C6.2, C7.2, P1.1, P2.1, P3.1, P4.1, P5.1, P6.1, P7.1, P8.1, P9.1, P10.1, P11.1, P12.1, P13.1, P22.1, P26.1, R9.2, R12.1, R26.1, SW1.2, SW2.2, U1.1 (GND/ADJ), U2.15 (GND), U3.8 (GND), U4.5 (GND), U5.5 (GND), U6.2 (GND)
GPIO0: R22.1, SW2.1, U2.18 (GPIO0), U3.1 (Pl)
GPIO2: R21.1, U2.17 (GPIO2), U3.2 (CP)
GPIO15: R12.2, U2.16 (GPIO15)
ID_0: P1.2, RP1.1
ID_1: P2.2, RP1.2
ID_2: P4.2, RP1.3
ID_3: P7.2, RP1.4
ID_4: P8.2, RP2.1
ID_5: P9.2, RP2.2
ID_6: P10.2, RP2.3
ID_7: P11.2, RP2.4
ID_DATA: U2.6 (GPIO12), U3.10 (Ds)
LED_CLOCK: P17.1, P17.2, Q1.2 (S), Q1.3 (D), R2.1, R13.1, R15.1, U2.20 (GPIO5)
LED_DATA: P18.1, P18.2, Q2.2 (S), Q2.3 (D), R1.1, R14.1, R16.1, U2.19 (GPIO4)
unnamed: P12.2, R1.2
unnamed: P12.3, R2.2
unnamed: P15.2, R3.2
unnamed: R9.1, U3.15 (CE)
unnamed: R11.1, U2.3 (CH_PD)
unnamed: RP1.5 (R4), U3.14 (P3)
unnamed: RP1.6 (R3), U3.13 (P2)
unnamed: RP1.7 (R2), U3.12 (P1)
unnamed: RP1.8 (R1), U3.11 (P0)
unnamed: RP2.5 (R4), U3.6 (P7)
unnamed: RP2.6 (R3), U3.5 (P6)
unnamed: RP2.7 (R2), U3.4 (P5)
unnamed: RP2.8 (R1), U3.3 (P4)
READER1: P3.2, U2.5 (GPIO14)
READER2: P3.3, U2.4 (GPIO16)
RESET: R10.1, SW1.1, U2.1 (RESET)
RX33: P13.4, P21.1, Q5.2 (S), R23.1, U2.21 (RXD0), U4.1 (RO)
RX50: P21.2, Q5.3 (D), R24.1, U5.1 (RO)
TX33: P13.5, P19.1, Q3.2 (S), R17.1, U2.22 (TXD0), U4.4 (DI)
TX50: P19.2, Q3.3 (D), R19.1, U5.4 (DI)
V12: C1.1, C3.1, C4.1, P5.4, P6.4, P12.4, P16.1, P25.1, P29.1, R25.2, U1.3 (VI), U6.3 (IN)
V33: C2.1, C5.1, C7.1, P1.3, P2.3, P3.4, P4.3, P7.3, P8.3, P9.3, P10.3, P11.3, P13.3, Q1.1 (G), Q2.1 (G), Q3.1 (G), Q4.1 (G), Q5.1 (G), R10.2, R11.2, R13.2, R14.2, R17.2, R18.2, R21.2, R22.2, R23.2, U1.2 (VO), U1.4 (VO), U2.8 (VCC), U3.16 (VCC), U4.8 (VCC)
V50: C6.1, P14.1, P16.2, R15.2, R16.2, R19.2, R20.2, R24.2, U5.8 (VCC), U6.1 (OUT)
V50D: P14.2, R25.1, R26.2

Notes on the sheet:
2-6V Supply for SN74HC165D
ESP8266 GPIO15 pull down GPIO0 pull up, switch to gnd GPIO2 pull up 0,2,15 Only as Outputs Can't use SPI
SP3485 is 3.3V LOW is Receive GPIO15 is already default LOW But need to pull high for 5V Level Shifting
MAX485 Module is 5V HIGH is 3.5V Can't use GPIO15 due to MOSFET pull up
Voltage Divider For 5V supply if needed
ESP8266 GPIO Max Current is 12mA 3.3/12mA = 275 Ohm 1K Ohm OK
Bridge 12V to 5V If Input Voltage is actually 5V
END Node should use a resistor to decrease reflections
Default Directly Connected
